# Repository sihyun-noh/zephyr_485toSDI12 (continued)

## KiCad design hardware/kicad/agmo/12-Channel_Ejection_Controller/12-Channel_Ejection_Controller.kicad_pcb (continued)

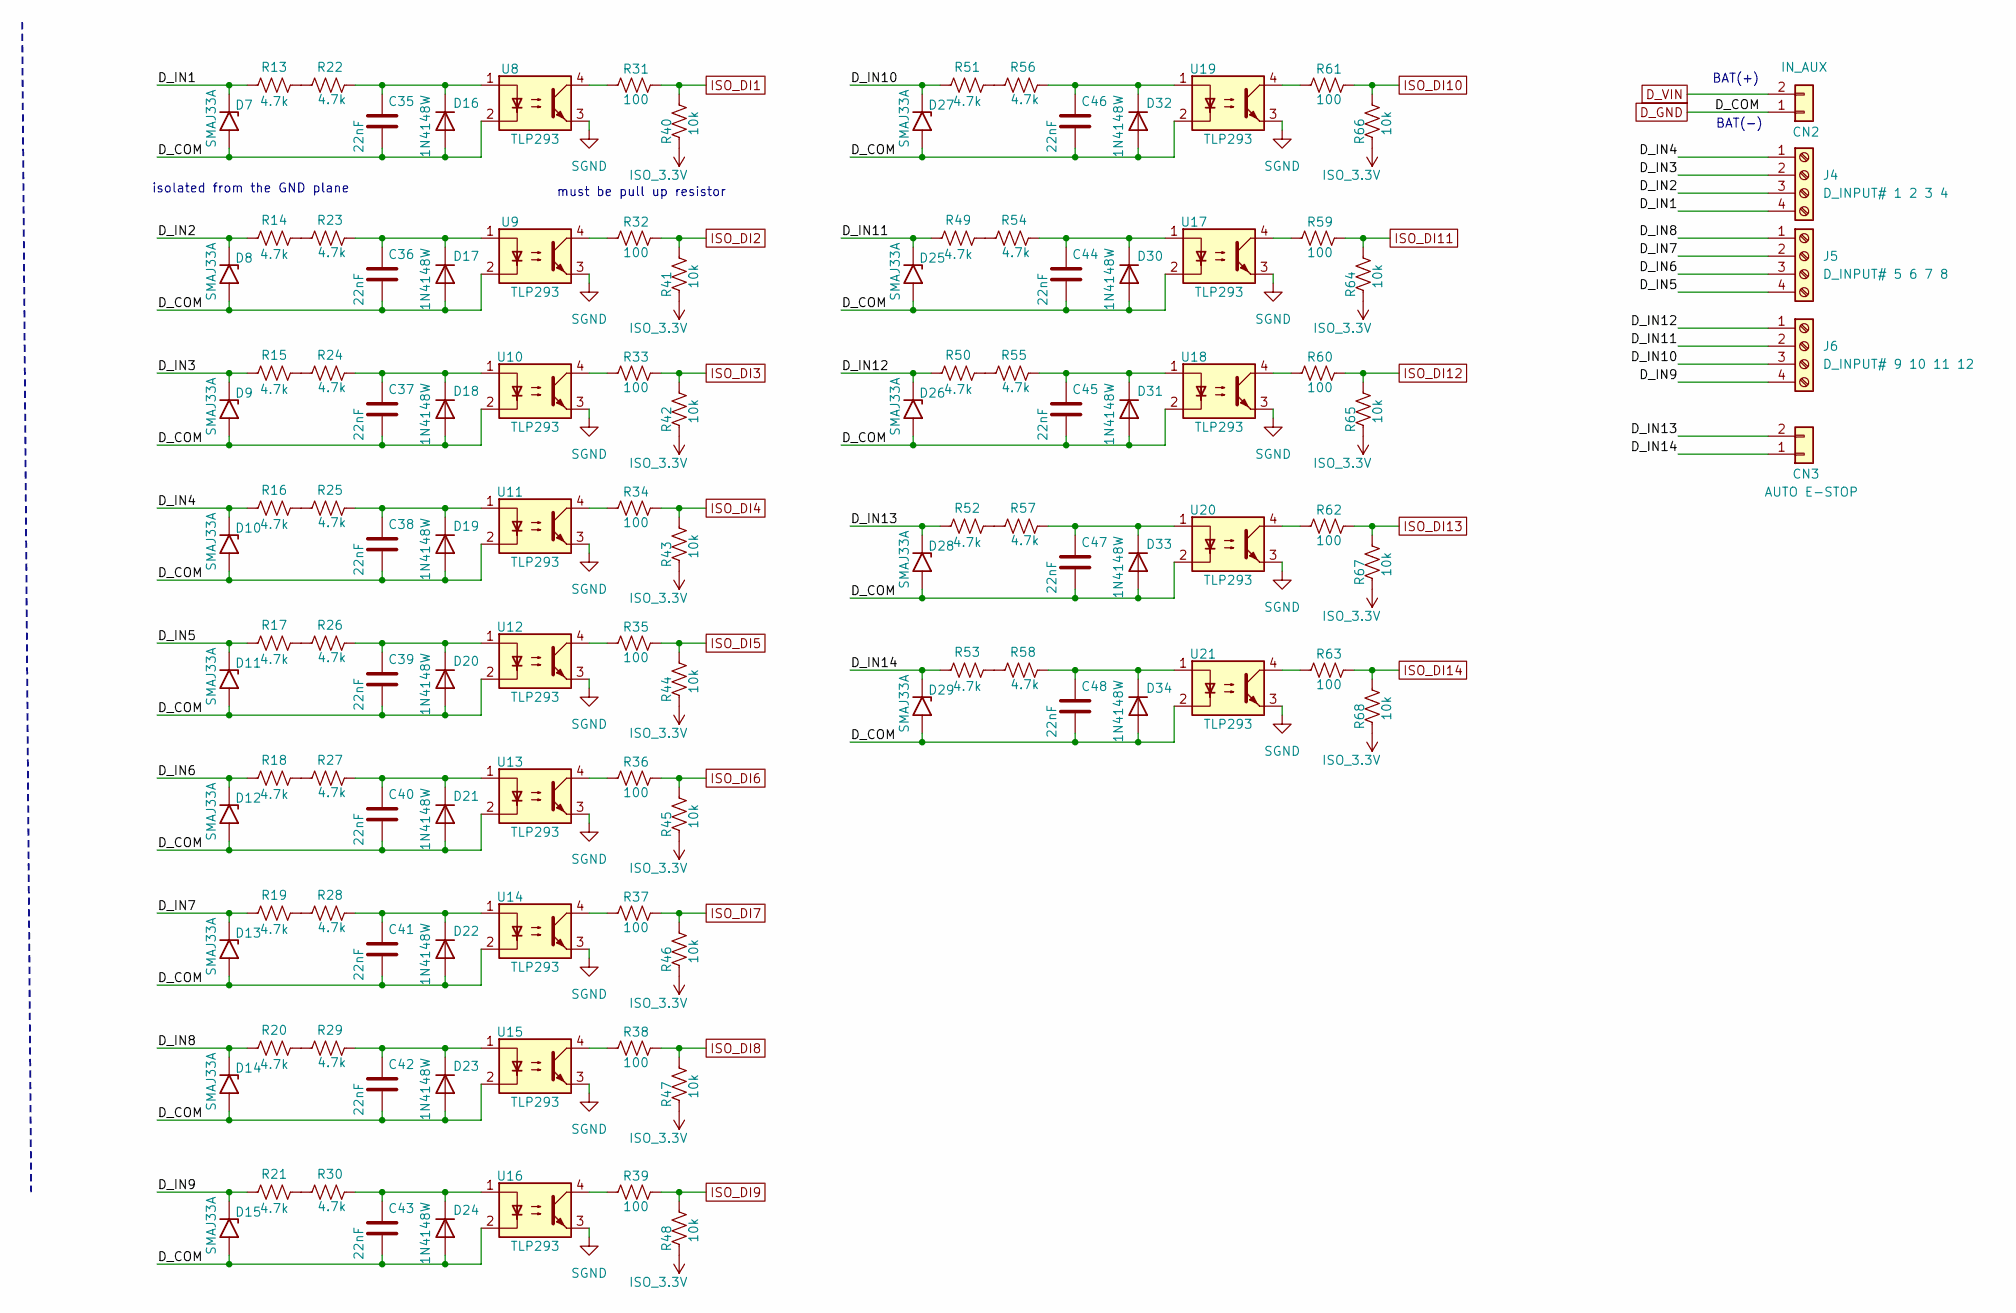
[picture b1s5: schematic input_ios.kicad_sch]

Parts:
C35, C36, C37, C38, C39, C40, C41, C42, C43, C44, C45, C46, C47, C48: 22nF; C_0805_2012Metric_Pad1.18x1.45mm_HandSolder
CN2: IN_AUX; PhoenixContact_MSTBA_2,5_2-G-5,08_1x02_P5.08mm_Horizontal; LCSC C395737
CN3: AUTO E-STOP; PhoenixContact_MSTBA_2,5_2-G-5,08_1x02_P5.08mm_Horizontal; LCSC C395737
D7, D8, D9, D10, D11, D12, D13, D14, D15, D25, D26, D27, D28, D29: SMAJ33A; D_SMA
D16, D17, D18, D19, D20, D21, D22, D23, D24, D30, D31, D32, D33, D34: 1N4148W; D_SOD-123
J4: D_INPUT# 1 2 3 4; PhoenixContact_MSTBA_2,5_4-G-5,08_1x04_P5.08mm_Horizontal; LCSC C395753
J5: D_INPUT# 5 6 7 8; PhoenixContact_MSTBA_2,5_4-G-5,08_1x04_P5.08mm_Horizontal; LCSC C395753
J6: D_INPUT# 9 10 11 12; PhoenixContact_MSTBA_2,5_4-G-5,08_1x04_P5.08mm_Horizontal; LCSC C395753
R13, R14, R15, R16, R17, R18, R19, R20, R21, R22, R23, R24, R25, R26, R27, R28, R29, R30, R49, R50, R51, R52, R53, R54, R55, R56, R57, R58: 4.7k; R_0805_2012Metric
R31, R32, R33, R34, R35, R36, R37, R38, R39, R59, R60, R61, R62, R63: 100; R_0805_2012Metric
R40, R41, R42, R43, R44, R45, R46, R47, R48, R64, R65, R66, R67, R68: 10k; R_0805_2012Metric
U8, U9, U10, U11, U12, U13, U14, U15, U16, U17, U18, U19, U20, U21: TLP293; SOIC-4_4.55x2.6mm_P1.27mm; LCSC C77656

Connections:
/input_ios Sheet/D_IN1: D7.1 (A1), J4.4, R13.1
/input_ios Sheet/D_IN2: D8.1 (A1), J4.3, R14.1
/input_ios Sheet/D_IN3: D9.1 (A1), J4.2, R15.1
/input_ios Sheet/D_IN4: D10.1 (A1), J4.1, R16.1
/input_ios Sheet/D_IN5: D11.1 (A1), J5.4, R17.1
/input_ios Sheet/D_IN6: D12.1 (A1), J5.3, R18.1
/input_ios Sheet/D_IN7: D13.1 (A1), J5.2, R19.1
/input_ios Sheet/D_IN8: D14.1 (A1), J5.1, R20.1
/input_ios Sheet/D_IN9: D15.1 (A1), J6.4, R21.1
/input_ios Sheet/D_IN10: D27.1 (A1), J6.3, R51.1
/input_ios Sheet/D_IN11: D25.1 (A1), J6.2, R49.1
/input_ios Sheet/D_IN12: D26.1 (A1), J6.1, R50.1
/input_ios Sheet/D_IN13: CN3.2, D28.1 (A1), R52.1
/input_ios Sheet/D_IN14: CN3.1, D29.1 (A1), R53.1
D_GND: C35.2, C36.2, C37.2, C38.2, C39.2, C40.2, C41.2, C42.2, C43.2, C44.2, C45.2, C46.2, C47.2, C48.2, CN2.1, D7.2 (A2), D8.2 (A2), D9.2 (A2), D10.2 (A2), D11.2 (A2), D12.2 (A2), D13.2 (A2), D14.2 (A2), D15.2 (A2), D16.2 (A), D17.2 (A), D18.2 (A), D19.2 (A), D20.2 (A), D21.2 (A), D22.2 (A), D23.2 (A), D24.2 (A), D25.2 (A2), D26.2 (A2), D27.2 (A2), D28.2 (A2), D29.2 (A2), D30.2 (A), D31.2 (A), D32.2 (A), D33.2 (A), D34.2 (A), U8.2, U9.2, U10.2, U11.2, U12.2, U13.2, U14.2, U15.2, U16.2, U17.2, U18.2, U19.2, U20.2, U21.2; also elsewhere on the board
D_VIN: CN2.2; also elsewhere on the board
ISO_3.3V: R40.2, R41.2, R42.2, R43.2, R44.2, R45.2, R46.2, R47.2, R48.2, R64.2, R65.2, R66.2, R67.2, R68.2; also elsewhere on the board
ISO_DI1: R31.1, R40.1; also elsewhere on the board
ISO_DI2: R32.1, R41.1; also elsewhere on the board
ISO_DI3: R33.1, R42.1; also elsewhere on the board
ISO_DI4: R34.1, R43.1; also elsewhere on the board
ISO_DI5: R35.1, R44.1; also elsewhere on the board
ISO_DI6: R36.1, R45.1; also elsewhere on the board
ISO_DI7: R37.1, R46.1; also elsewhere on the board
ISO_DI8: R38.1, R47.1; also elsewhere on the board
ISO_DI9: R39.1, R48.1; also elsewhere on the board
ISO_DI10: R61.1, R66.1; also elsewhere on the board
ISO_DI11: R59.1, R64.1; also elsewhere on the board
ISO_DI12: R60.1, R65.1; also elsewhere on the board
ISO_DI13: R62.1, R67.1; also elsewhere on the board
ISO_DI14: R63.1, R68.1; also elsewhere on the board
unnamed: C35.1, D16.1 (K), R22.2, U8.1
unnamed: C36.1, D17.1 (K), R23.2, U9.1
unnamed: C37.1, D18.1 (K), R24.2, U10.1
unnamed: C38.1, D19.1 (K), R25.2, U11.1
unnamed: C39.1, D20.1 (K), R26.2, U12.1
unnamed: C40.1, D21.1 (K), R27.2, U13.1
unnamed: C41.1, D22.1 (K), R28.2, U14.1
unnamed: C42.1, D23.1 (K), R29.2, U15.1
unnamed: C43.1, D24.1 (K), R30.2, U16.1
unnamed: C44.1, D30.1 (K), R54.2, U17.1
unnamed: C45.1, D31.1 (K), R55.2, U18.1
unnamed: C46.1, D32.1 (K), R56.2, U19.1
unnamed: C47.1, D33.1 (K), R57.2, U20.1
unnamed: C48.1, D34.1 (K), R58.2, U21.1
unnamed: R13.2, R22.1
unnamed: R14.2, R23.1
unnamed: R15.2, R24.1
unnamed: R16.2, R25.1
unnamed: R17.2, R26.1
unnamed: R18.2, R27.1
unnamed: R19.2, R28.1
unnamed: R20.2, R29.1
unnamed: R21.2, R30.1
unnamed: R31.2, U8.4
unnamed: R32.2, U9.4
unnamed: R33.2, U10.4
unnamed: R34.2, U11.4
unnamed: R35.2, U12.4
unnamed: R36.2, U13.4
unnamed: R37.2, U14.4
unnamed: R38.2, U15.4
unnamed: R39.2, U16.4
unnamed: R49.2, R54.1
unnamed: R50.2, R55.1
unnamed: R51.2, R56.1
unnamed: R52.2, R57.1
unnamed: R53.2, R58.1
unnamed: R59.2, U17.4
unnamed: R60.2, U18.4
unnamed: R61.2, U19.4
unnamed: R62.2, U20.4
unnamed: R63.2, U21.4
SGND: U8.3, U9.3, U10.3, U11.3, U12.3, U13.3, U14.3, U15.3, U16.3, U17.3, U18.3, U19.3, U20.3, U21.3; also elsewhere on the board

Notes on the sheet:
isolated from the GND plane
BAT(+)
BAT(-)
must be pull up resistor

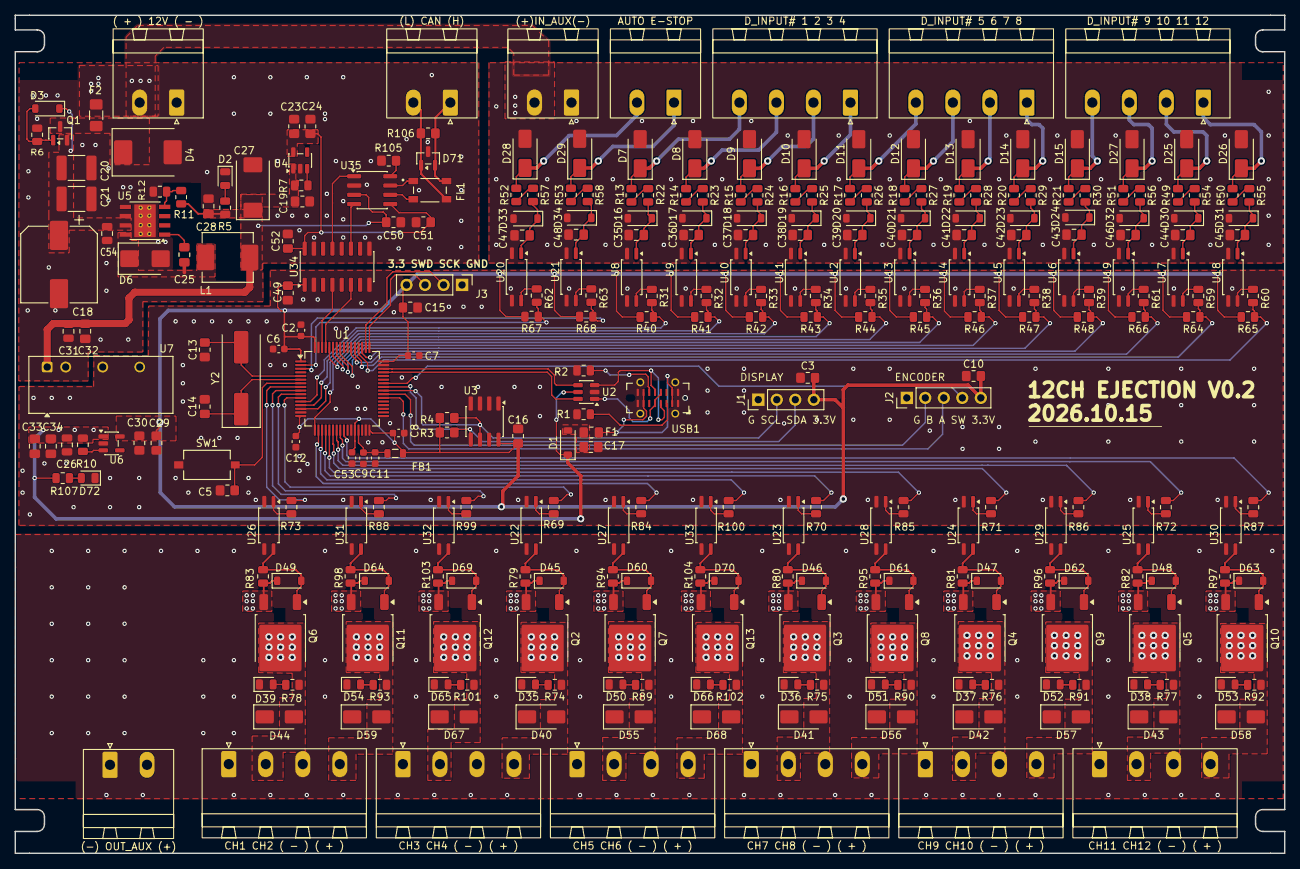
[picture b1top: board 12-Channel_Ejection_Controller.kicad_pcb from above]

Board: 2 copper layers, 174.2 x 115.0 mm, 300 parts (0 on the bottom side), 177 nets.

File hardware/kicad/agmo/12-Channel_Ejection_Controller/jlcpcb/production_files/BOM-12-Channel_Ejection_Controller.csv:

Comment,Designator,Footprint,LCSC,Quantity
( + ) 12V ( - ),CN1,"PhoenixContact_MSTBA_2,5_2-G-5,08_1x02_P5.08mm_Horizontal",C395737,1
(+)IN_AUX(-),CN2,"PhoenixContact_MSTBA_2,5_2-G-5,08_1x02_P5.08mm_Horizontal",C395737,1
(-) OUT_AUX (+),CN5,"PhoenixContact_MSTBA_2,5_2-G-5,08_1x02_P5.08mm_Horizontal",C395737,1
(L) CAN (H),CN4,"PhoenixContact_MSTBA_2,5_2-G-5,08_1x02_P5.08mm_Horizontal",C395737,1
0466005.NRHF,F2,Fuse_1206_3216Metric_Pad1.42x1.75mm_HandSolder,C57525,1
100,"R31,R32,R33,R34,R35,R36,R37,R38,R39,R59,R60,R61,R62,R63",R_0805_2012Metric,C17408,14
100nF,"C12,C2,C53,C6,C7,C8,C9",C_0603_1608Metric,C1591,7
100nF,"C10,C15,C16,C17,C23,C28,C29,C3,C32,C34,C49,C5,C50,C51,C52,C54",R_0805_2012Metric_Pad1.20x1.40mm_HandSolder,C1711,16
10k,"R1,R10,R11,R2,R40,R41,R42,R43,R44,R45,R46,R47,R48,R64,R65,R66,R67,R68,R7",R_0805_2012Metric,C17414,19
10nF,C25,C_0805_2012Metric_Pad1.18x1.45mm_HandSolder,C97905,1
10uF,C33,C_0805_2012Metric_Pad1.18x1.45mm_HandSolder,C15850,1
10uF/50V,C20,C_1812_4532Metric,C76689,1
120,R106,R_0805_2012Metric_Pad1.20x1.40mm_HandSolder,C17437,1
1N4148W,"D16,D17,D18,D19,D20,D21,D22,D23,D24,D30,D31,D32,D33,D34",D_SOD-123,C2099,14
1N5819,D1,D_SOD-123,C963381,1
1k,"R100,R69,R70,R71,R72,R73,R84,R85,R86,R87,R88,R99",R_0805_2012Metric,C17513,12
1uF,C11,C_0603_1608Metric,C15849,1
1uF,"C19,C24,C30",R_0805_2012Metric_Pad1.20x1.40mm_HandSolder,C1712,3
220uF,C27,CP_EIA-7343-31_Kemet-D,C130380,1
220uF/50V,C18,CP_Elec_10x10,C125976,1
22k,"R103,R104,R79,R80,R81,R82,R83,R94,R95,R96,R97,R98",R_0805_2012Metric,C17560,12
22nF,"C35,C36,C37,C38,C39,C40,C41,C42,C43,C44,C45,C46,C47,C48",C_0805_2012Metric_Pad1.18x1.45mm_HandSolder,C1729,14
22pF,"C13,C14",R_0805_2012Metric_Pad1.20x1.40mm_HandSolder,C1804,2
22uH,L1,L_APV_APH0630,C5349702,1
3.24k,R12,R_0805_2012Metric,C17609,1
4.7k,"R101,R102,R107,R13,R14,R15,R16,R17,R18,R19,R20,R21,R22,R23,R24,R25,R26,R27,R28,R29,R3,R30,R4,R49,R5,R50,R51,R52,R53,R54,R55,R56,R57,R58,R6,R74,R75,R76,R77,R78,R89,R90,R91,R92,R93",R_0805_2012Metric,C17673,45
4.7uF,"C26,C31",C_0805_2012Metric,C1779,2
4.7uF/50V,C21,C_1812_4532Metric,C342629,1
600Ω @ 100MHz,FB1,L_0805_2012Metric,C21519,1
8Mhz,Y2,Crystal_SMD_HC49-SD,C12674,1
ACT45B-510-2P-TL003,FL1,FIL_ACT45B-510-2P-TL003,C76584,1
AP2112K-3.3,"U4,U6",SOT-23-5,C51118,2
AT24C256C-SSHL,U3,SOIC-8_3.9x4.9mm_P1.27mm,C615461,1
AUTO E-STOP,CN3,"PhoenixContact_MSTBA_2,5_2-G-5,08_1x02_P5.08mm_Horizontal",C395737,1
B0505S-3W,U7,Converter_DCDC_TRACO_TBA2-xxxx_Single_THT,C7465195,1
B340,D6,D_SMB,C3018525,1
BZT52C15,"D3,D45,D46,D47,D48,D49,D60,D61,D62,D63,D64,D69,D70",D_SOD-123,C2932746,13
CH1 CH2 ( - ) ( + ),J7,"PhoenixContact_MSTBA_2,5_4-G-5,08_1x04_P5.08mm_Horizontal",C395753,1
CH11 CH12 ( - ) ( + ),J12,"PhoenixContact_MSTBA_2,5_4-G-5,08_1x04_P5.08mm_Horizontal",C395753,1
CH3 CH4 ( - ) ( + ),J9,"PhoenixContact_MSTBA_2,5_4-G-5,08_1x04_P5.08mm_Horizontal",C395753,1
CH5 CH6 ( - ) ( + ),J11,"PhoenixContact_MSTBA_2,5_4-G-5,08_1x04_P5.08mm_Horizontal",C395753,1
CH7 CH8 ( - ) ( + ),J8,"PhoenixContact_MSTBA_2,5_4-G-5,08_1x04_P5.08mm_Horizontal",C395753,1
CH9 CH10 ( - ) ( + ),J10,"PhoenixContact_MSTBA_2,5_4-G-5,08_1x04_P5.08mm_Horizontal",C395753,1
DMP10H400SK3-13,"Q10,Q11,Q12,Q13,Q2,Q3,Q4,Q5,Q6,Q7,Q8,Q9",TO-252-2,C177034,12
D_INPUT# 1 2 3 4,J4,"PhoenixContact_MSTBA_2,5_4-G-5,08_1x04_P5.08mm_Horizontal",C395753,1
D_INPUT# 5 6 7 8,J5,"PhoenixContact_MSTBA_2,5_4-G-5,08_1x04_P5.08mm_Horizontal",C395753,1
D_INPUT# 9 10 11 12,J6,"PhoenixContact_MSTBA_2,5_4-G-5,08_1x04_P5.08mm_Horizontal",C395753,1
Debug,J3,PinHeader_1x04_P2.54mm_Vertical,C53207327,1
LED RED,"D2,D35,D36,D37,D38,D39,D50,D51,D52,D53,D54,D65,D66,D72",LED_0805_2012Metric,C2297,14
MF-PSMF050X-2,F1,C_0805_2012Metric_Pad1.18x1.45mm_HandSolder,C116170,1
NRST,SW1,SW_Tactile_SPST_NO_Straight_CK_PTS636Sx25SMTRLFS,C42420257,1
SM24CANB-02HTG,D71,SOT-23,C151237,1
SMAJ30CA,"D40,D41,D42,D43,D44,D55,D56,D57,D58,D59,D67,D68",D_SMA,C83322,12
SMAJ33A,"D10,D11,D12,D13,D14,D15,D25,D26,D27,D28,D29,D7,D8,D9",D_SMA,C223988,14
SMCJ18AC,D4,D_SMC,C374030,1
SQ2361CEES-T1_GE3,Q1,SOT-23,C29267586,1
SSD1309,J1,PinHeader_1x04_P2.54mm_Vertical,C53207327,1
STM32G473RCT6,U1,LQFP-64_10x10mm_P0.5mm,C529361,1
TJA1051T-3,U35,SOIC-8_3.9x4.9mm_P1.27mm,C38695,1
TLP293,"U10,U11,U12,U13,U14,U15,U16,U17,U18,U19,U20,U21,U22,U23,U24,U25,U26,U27,U28,U29,U30,U31,U32,U33,U8,U9",SOIC-4_4.55x2.6mm_P1.27mm,C77656,26
TPS5430DDA,U5,TI_SO-PowerPAD-8_ThermalVias,C9864,1
USBLC6-2SC6,U2,SOT-23-6,C2827654,1
USB_C_Receptacle_USB2.0_16P,USB1,USB_C_Receptacle_G-Switch_GT-USB-7051x,C2843970,1
encoder-key,J2,PinHeader_1x05_P2.54mm_Vertical,C53207329,1
π142M31,U34,SOIC-16_3.9x9.9mm_P1.27mm,C471606,1
0/J,R105,R_0805_2012Metric_Pad1.20x1.40mm_HandSolder,,1

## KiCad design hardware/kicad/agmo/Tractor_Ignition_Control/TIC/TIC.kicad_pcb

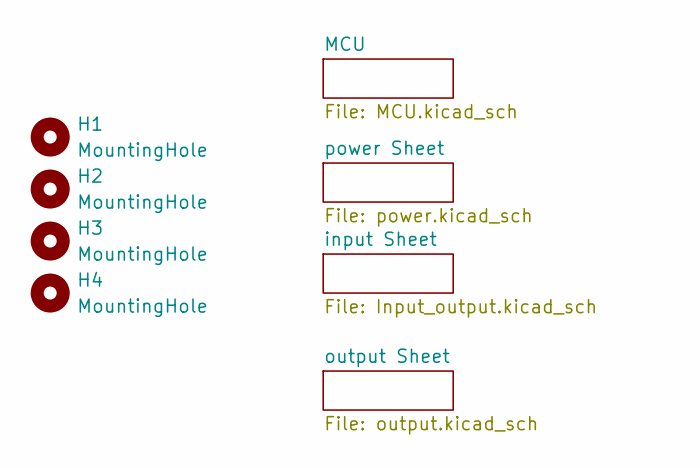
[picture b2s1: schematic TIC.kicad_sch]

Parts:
H1, H2, H3, H4: MountingHole; MountingHole_3.2mm_M3_ISO14580_Pad_TopBottom

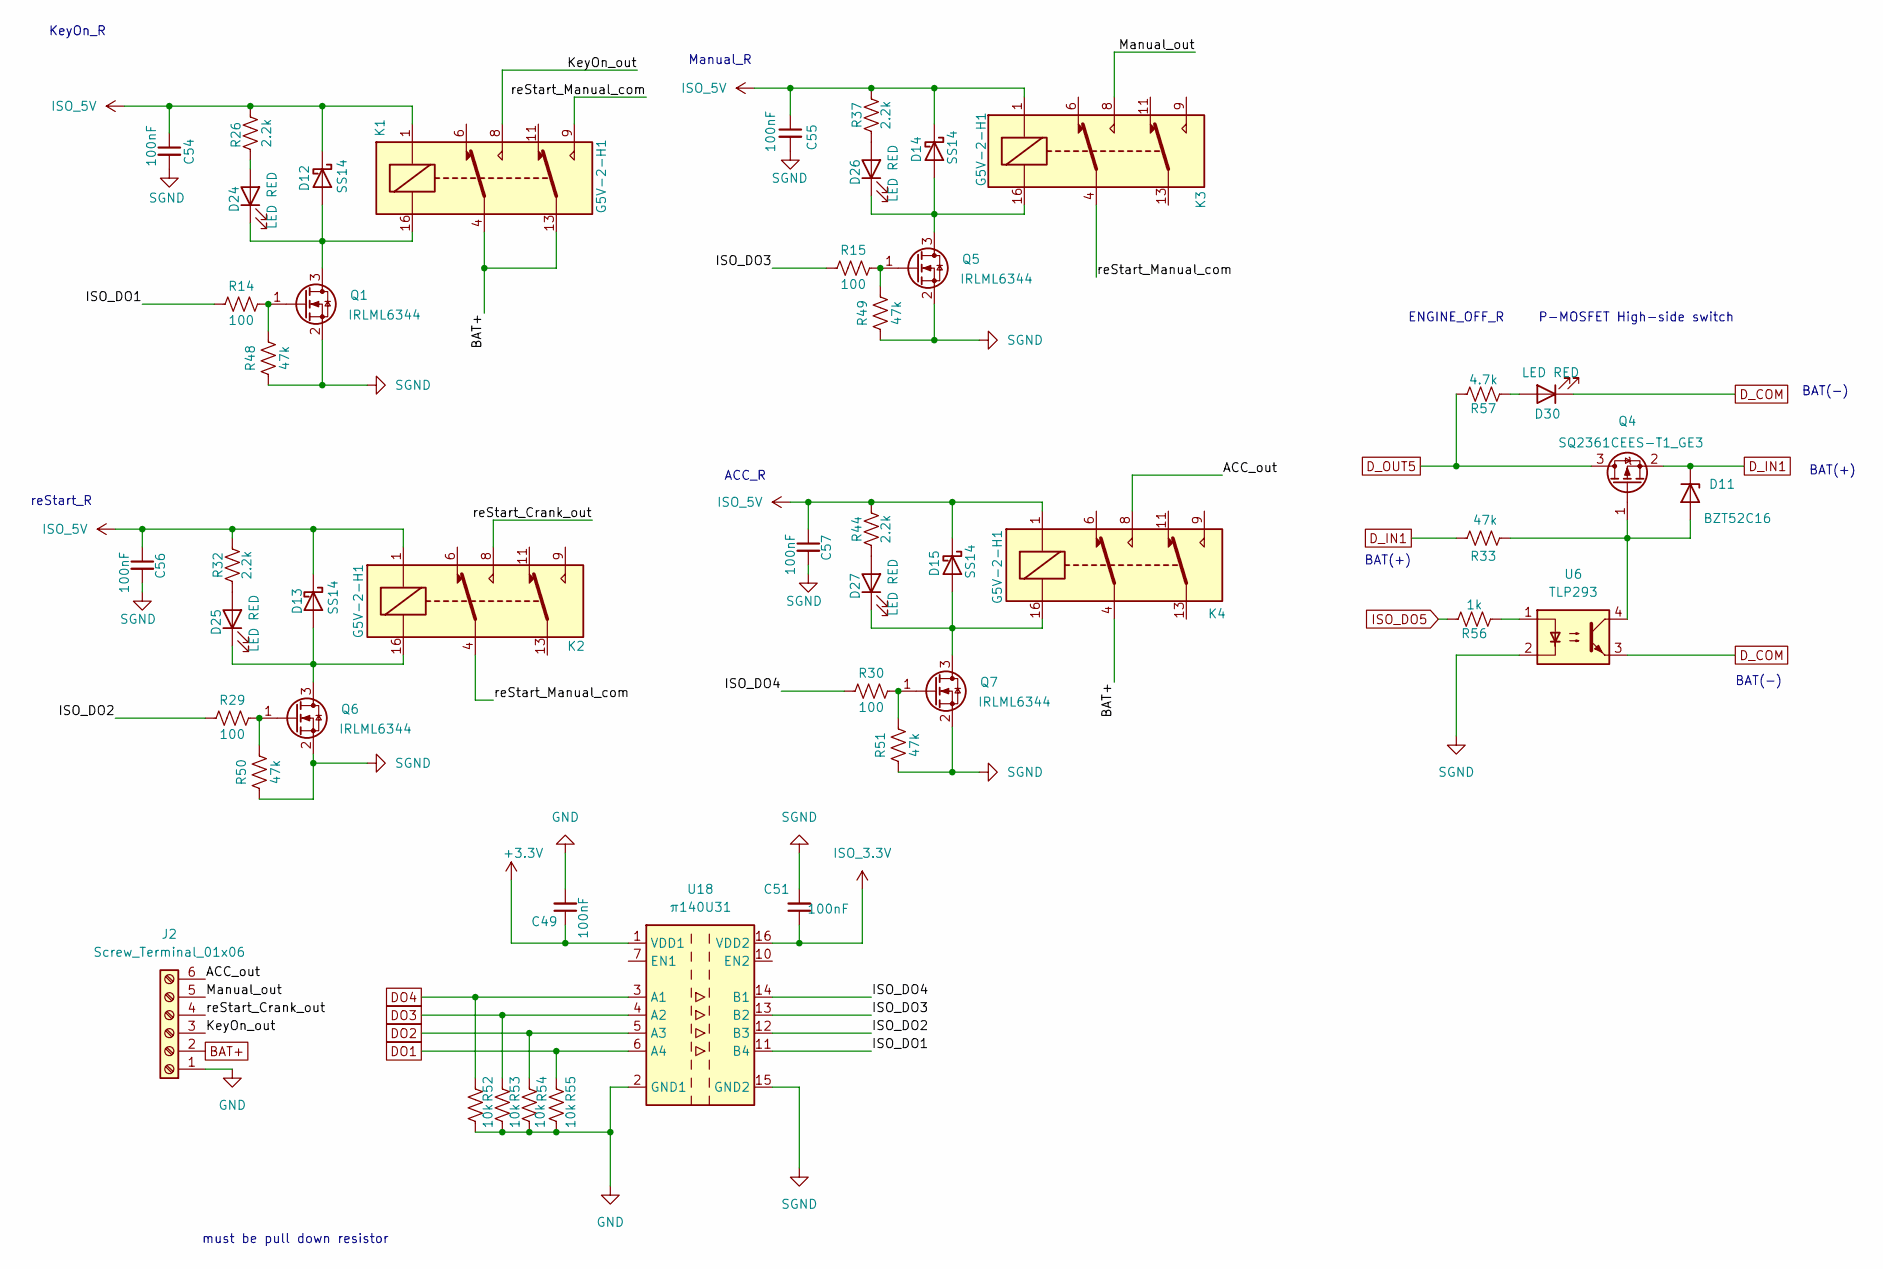
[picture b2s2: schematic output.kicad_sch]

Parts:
C49, C51: 100nF; R_0805_2012Metric_Pad1.20x1.40mm_HandSolder
C54, C55, C56, C57: 100nF; C_0805_2012Metric
D11: BZT52C16; D_SOD-123
D12, D13, D14, D15: SS14; D_SMA
D24, D25, D26, D27, D30: LED RED; LED_0805_2012Metric
J2: Screw_Terminal_01x06; PhoenixContact_MSTBA_2,5_6-G-5,08_1x06_P5.08mm_Horizontal; LCSC C395769
K1, K2, K3, K4: G5V-2-H1; Relay_DPDT_Omron_G5V-2
Q1, Q5, Q6, Q7: IRLML6344; SOT-23; LCSC C53550
Q4: SQ2361CEES-T1_GE3; SOT-23; LCSC C29267586
R14, R15, R29, R30: 100; R_0805_2012Metric
R26, R32, R37, R44: 2.2k; R_0805_2012Metric
R33, R48, R49, R50, R51: 47k; R_0805_2012Metric
R52, R53, R54, R55: 10k; R_0805_2012Metric
R56: 1k; R_0805_2012Metric
R57: 4.7k; R_0805_2012Metric
U6: TLP293; SOIC-4_4.55x2.6mm_P1.27mm; LCSC C77656
U18: π140U31; SOIC-16_3.9x9.9mm_P1.27mm; LCSC C471601

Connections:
+3.3V: C49.1, U18.1 (VDD1); also elsewhere on the board
/output Sheet/ACC_out: J2.6, K4.8
/output Sheet/ISO_DO1: R14.1, U18.11 (B4)
/output Sheet/ISO_DO2: R29.1, U18.12 (B3)
/output Sheet/ISO_DO3: R15.1, U18.13 (B2)
/output Sheet/ISO_DO4: R30.1, U18.14 (B1)
/output Sheet/KeyOn_out: J2.3, K1.8
/output Sheet/Manual_out: J2.5, K3.8
/output Sheet/reStart_Crank_out: J2.4, K2.8
/output Sheet/reStart_Manual_com: K1.9, K2.4, K3.4
DO1: R55.2, U18.6 (A4); also elsewhere on the board
DO2: R54.2, U18.5 (A3); also elsewhere on the board
DO3: R53.2, U18.4 (A2); also elsewhere on the board
DO4: R52.2, U18.3 (A1); also elsewhere on the board
D_COM: D30.1 (K), U6.3; also elsewhere on the board
D_IN1: D11.1 (K), Q4.2 (S), R33.2; also elsewhere on the board
D_OUT5: Q4.3 (D), R57.1; also elsewhere on the board
ISO_3.3V: C51.1, U18.16 (VDD2); also elsewhere on the board
ISO_5V: C54.1, C55.1, C56.1, C57.1, D12.1 (K), D13.1 (K), D14.1 (K), D15.1 (K), K1.1, K2.1, K3.1, K4.1, R26.1, R32.1, R37.1, R44.1; also elsewhere on the board
ISO_DO5: R56.1; also elsewhere on the board
unnamed: D11.2 (A), Q4.1 (G), R33.1, U6.4
unnamed: D12.2 (A), D24.1 (K), K1.16, Q1.3 (D)
unnamed: D13.2 (A), D25.1 (K), K2.16, Q6.3 (D)
unnamed: D14.2 (A), D26.1 (K), K3.16, Q5.3 (D)
unnamed: D15.2 (A), D27.1 (K), K4.16, Q7.3 (D)
unnamed: D24.2 (A), R26.2
unnamed: D25.2 (A), R32.2
unnamed: D26.2 (A), R37.2
unnamed: D27.2 (A), R44.2
unnamed: D30.2 (A), R57.2
unnamed: Q1.1 (G), R14.2, R48.2
unnamed: Q5.1 (G), R15.2, R49.2
unnamed: Q6.1 (G), R29.2, R50.2
unnamed: Q7.1 (G), R30.2, R51.2
unnamed: R56.2, U6.1
SGND: C51.2, C54.2, C55.2, C56.2, C57.2, Q1.2 (S), Q5.2 (S), Q6.2 (S), Q7.2 (S), R48.1, R49.1, R50.1, R51.1, U6.2, U18.9 (GND2), U18.15 (GND2); also elsewhere on the board

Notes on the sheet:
ACC_R
Manual_R
must be pull down resistor
BAT(-)
KeyOn_R
reStart_R
ENGINE_OFF_R
P-MOSFET High-side switch
BAT(+)

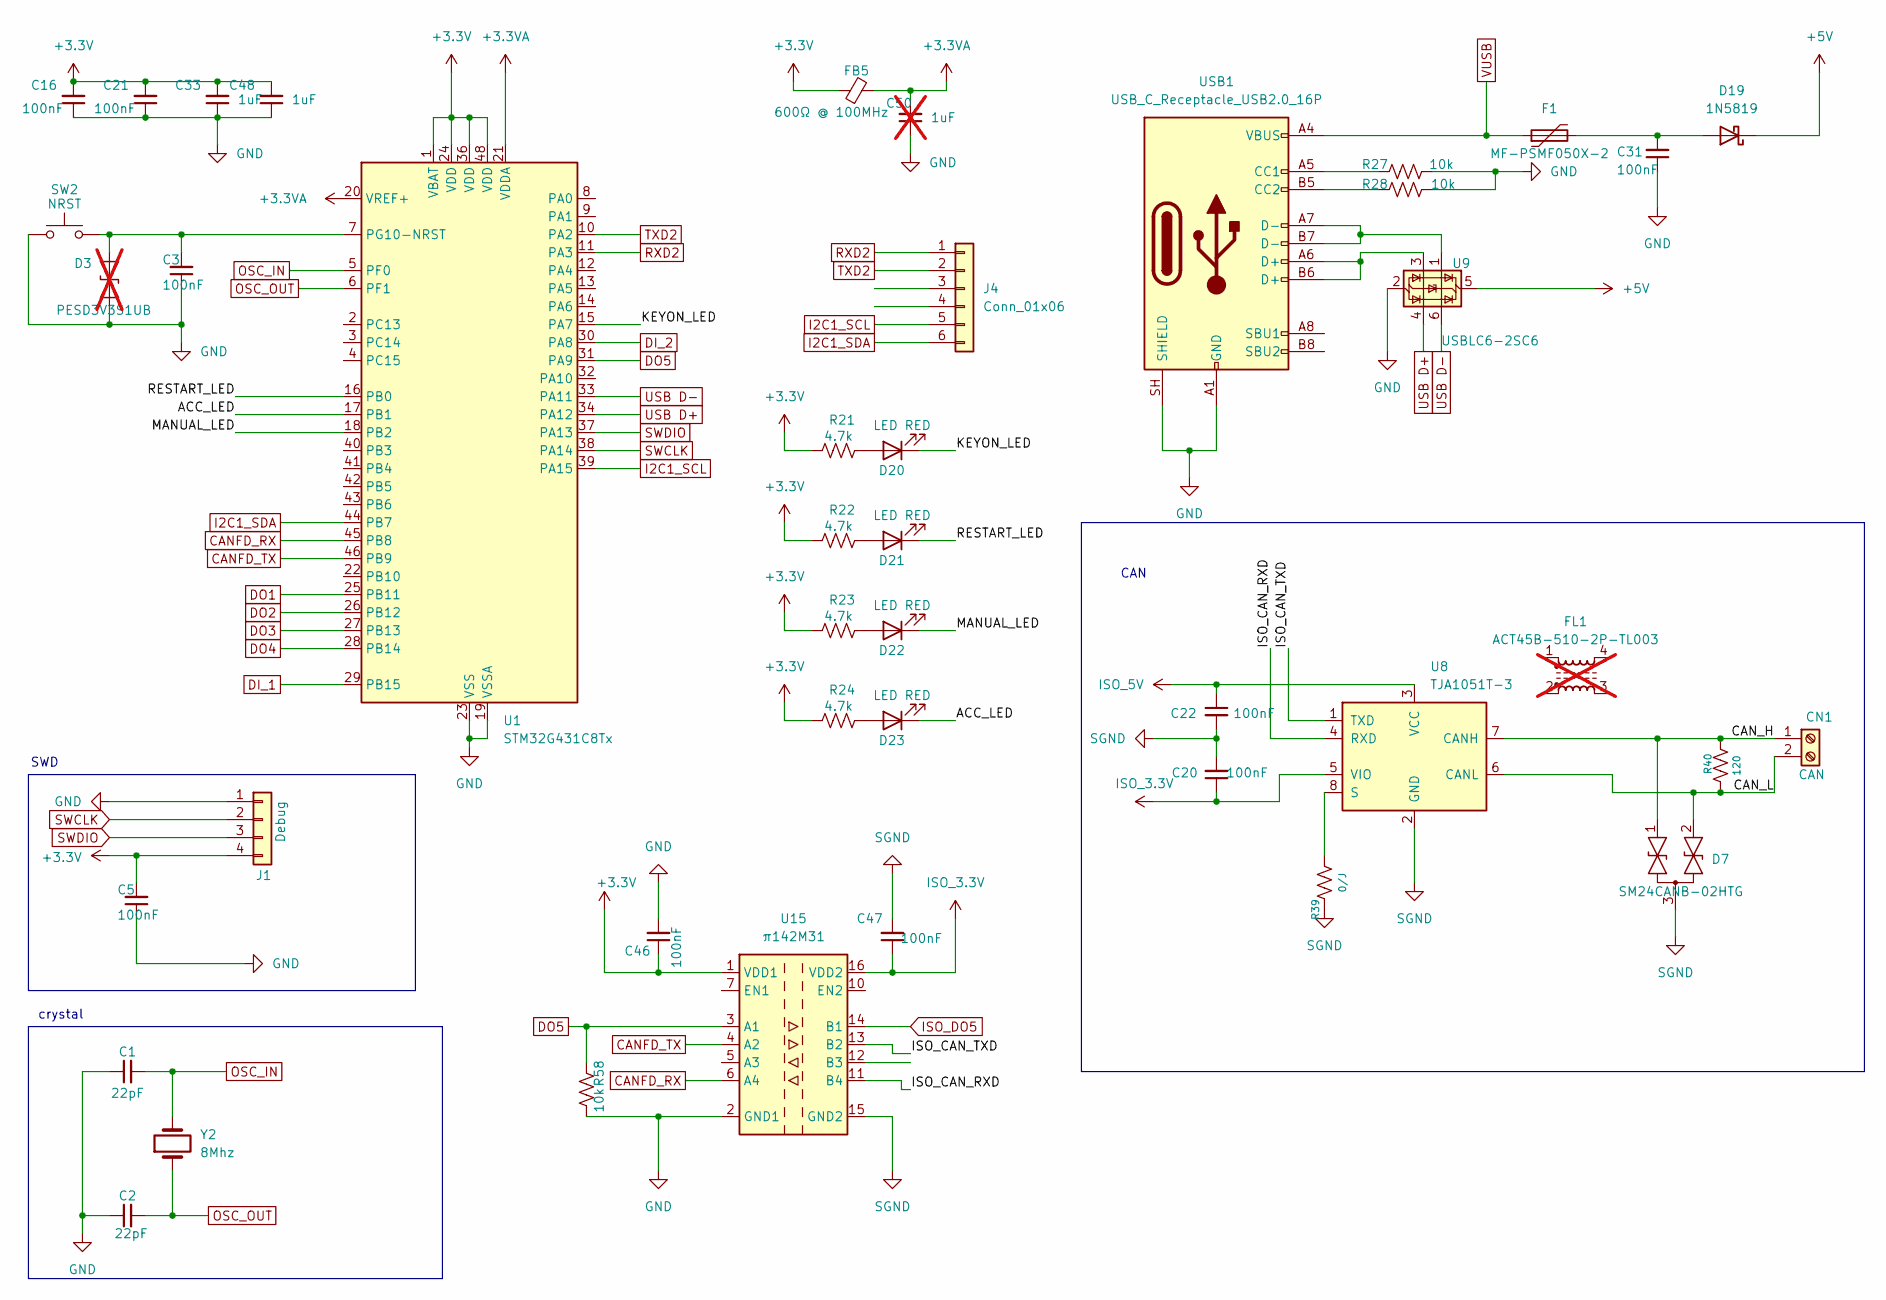
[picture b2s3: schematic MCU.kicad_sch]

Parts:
C1, C2: 22pF; R_0805_2012Metric_Pad1.20x1.40mm_HandSolder
C3, C5, C16, C20, C21, C22, C31, C46, C47: 100nF; R_0805_2012Metric_Pad1.20x1.40mm_HandSolder
C33, C48: 1uF; R_0805_2012Metric_Pad1.20x1.40mm_HandSolder
C50: 1uF; R_0805_2012Metric_Pad1.20x1.40mm_HandSolder; not fitted
CN1: CAN; PhoenixContact_MSTBA_2,5_2-G-5,08_1x02_P5.08mm_Horizontal; LCSC C395737
D3: PESD3V3S1UB; D_SOD-923; LCSC C7436896; not fitted
D7: SM24CANB-02HTG; SOT-23
D19: 1N5819; D_SOD-323
D20, D21, D22, D23: LED RED; LED_0805_2012Metric
F1: MF-PSMF050X-2; C_0805_2012Metric_Pad1.18x1.45mm_HandSolder; LCSC C116170
FB5: 600Ω @ 100MHz; L_0805_2012Metric_Pad1.05x1.20mm_HandSolder; LCSC C81034
FL1: ACT45B-510-2P-TL003; L_CommonModeChoke_Coilank_ACM3216; not fitted
J1: Debug; PinHeader_1x04_P2.54mm_Vertical
J4: Conn_01x06
R21, R22, R23, R24: 4.7k; R_0805_2012Metric
R27, R28, R58: 10k; R_0805_2012Metric
R39: 0/J; R_0805_2012Metric_Pad1.20x1.40mm_HandSolder
R40: 120; R_0805_2012Metric_Pad1.20x1.40mm_HandSolder
SW2: NRST; SW_Tactile_SPST_NO_Straight_CK_PTS636Sx25SMTRLFS; LCSC C42420257
U1: STM32G431C8Tx; LQFP-48_7x7mm_P0.5mm
U8: TJA1051T-3; SOIC-8_3.9x4.9mm_P1.27mm; LCSC C38695
U9: USBLC6-2SC6; SOT-23-6; LCSC C2827654
U15: π142M31; SOIC-16_3.9x9.9mm_P1.27mm; LCSC C471606
USB1: USB_C_Receptacle_USB2.0_16P; USB_C_Receptacle_G-Switch_GT-USB-7010ASV; LCSC C2988369
Y2: 8Mhz; Crystal_SMD_HC49-SD; LCSC C12674

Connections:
+3.3V: C5.2, C16.2, C21.2, C33.2, C46.1, C48.2, FB5.1, J1.4, R21.2, R22.2, R23.2, R24.2, U1.1 (VBAT), U1.24 (VDD), U1.36 (VDD), U1.48 (VDD), U15.1 (VDD1); also elsewhere on the board
+3.3VA: C50.2, FB5.2, U1.20 (VREF+), U1.21 (VDDA)
+5V: D19.1 (K), U9.5 (VBUS); also elsewhere on the board
/MCU/ACC_LED: D23.1 (K), U1.17 (PB1); also elsewhere on the board
/MCU/CAN_H: CN1.1, D7.1 (A1), R40.2, U8.7 (CANH)
/MCU/CAN_L: CN1.2, D7.2 (A2), R40.1, U8.6 (CANL)
/MCU/ISO_CAN_RXD: U8.4 (RXD), U15.11 (B4)
/MCU/ISO_CAN_TXD: U8.1 (TXD), U15.13 (B2)
/MCU/KEYON_LED: D20.1 (K), U1.15 (PA7); also elsewhere on the board
/MCU/MANUAL_LED: D22.1 (K), U1.18 (PB2); also elsewhere on the board
/MCU/RESTART_LED: D21.1 (K), U1.16 (PB0); also elsewhere on the board
CANFD_RX: U1.45 (PB8), U15.6 (A4)
CANFD_TX: U1.46 (PB9), U15.4 (A2)
DI_1: U1.29 (PB15); also elsewhere on the board
DI_2: U1.30 (PA8); also elsewhere on the board
DO1: U1.25 (PB11); also elsewhere on the board
DO2: U1.26 (PB12); also elsewhere on the board
DO3: U1.27 (PB13); also elsewhere on the board
DO4: U1.28 (PB14); also elsewhere on the board
DO5: R58.2, U1.31 (PA9), U15.3 (A1)
I2C1_SCL: J4.5, U1.39 (PA15)
I2C1_SDA: J4.6, U1.44 (PB7)
ISO_3.3V: C20.1, C47.1, U8.5 (VIO), U15.16 (VDD2); also elsewhere on the board
ISO_5V: C22.1, U8.3 (VCC); also elsewhere on the board
ISO_DO5: U15.14 (B1); also elsewhere on the board
unnamed: C31.2, D19.2 (A), F1.2
unnamed 55: D20.2 (A), R21.1; also elsewhere on the board
unnamed 56: D21.2 (A), R22.1; also elsewhere on the board
unnamed 57: D22.2 (A), R23.1; also elsewhere on the board
unnamed 58: D23.2 (A), R24.1; also elsewhere on the board
unnamed: C3.2, D3.1 (A1), SW2.2, U1.7 (PG10-NRST)
unnamed: R39.2, U8.8 (S)
unnamed: U9.1 (I/O1), USB1.A7 (D-), USB1.B7 (D-)
unnamed: U9.3 (I/O2), USB1.A6 (D+), USB1.B6 (D+)
unnamed: R27.1, USB1.A5 (CC1)
unnamed: R28.1, USB1.B5 (CC2)
OSC_IN: C1.2, U1.5 (PF0), Y2.2
OSC_OUT: C2.2, U1.6 (PF1), Y2.1
RXD2: J4.1, U1.11 (PA3)
SGND: C20.2, C22.2, C47.2, D7.3 (common), R39.1, U8.2 (GND), U15.9 (GND2), U15.15 (GND2); also elsewhere on the board
SWCLK: J1.2, U1.38 (PA14)
SWDIO: J1.3, U1.37 (PA13)
TXD2: J4.2, U1.10 (PA2)
USB D+: U1.34 (PA12), U9.4 (I/O2)
USB D-: U1.33 (PA11), U9.6 (I/O1)
VUSB: F1.1, USB1.A4 (VBUS), USB1.A9 (VBUS), USB1.B4 (VBUS), USB1.B9 (VBUS)

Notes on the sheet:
CAN
crystal
SWD

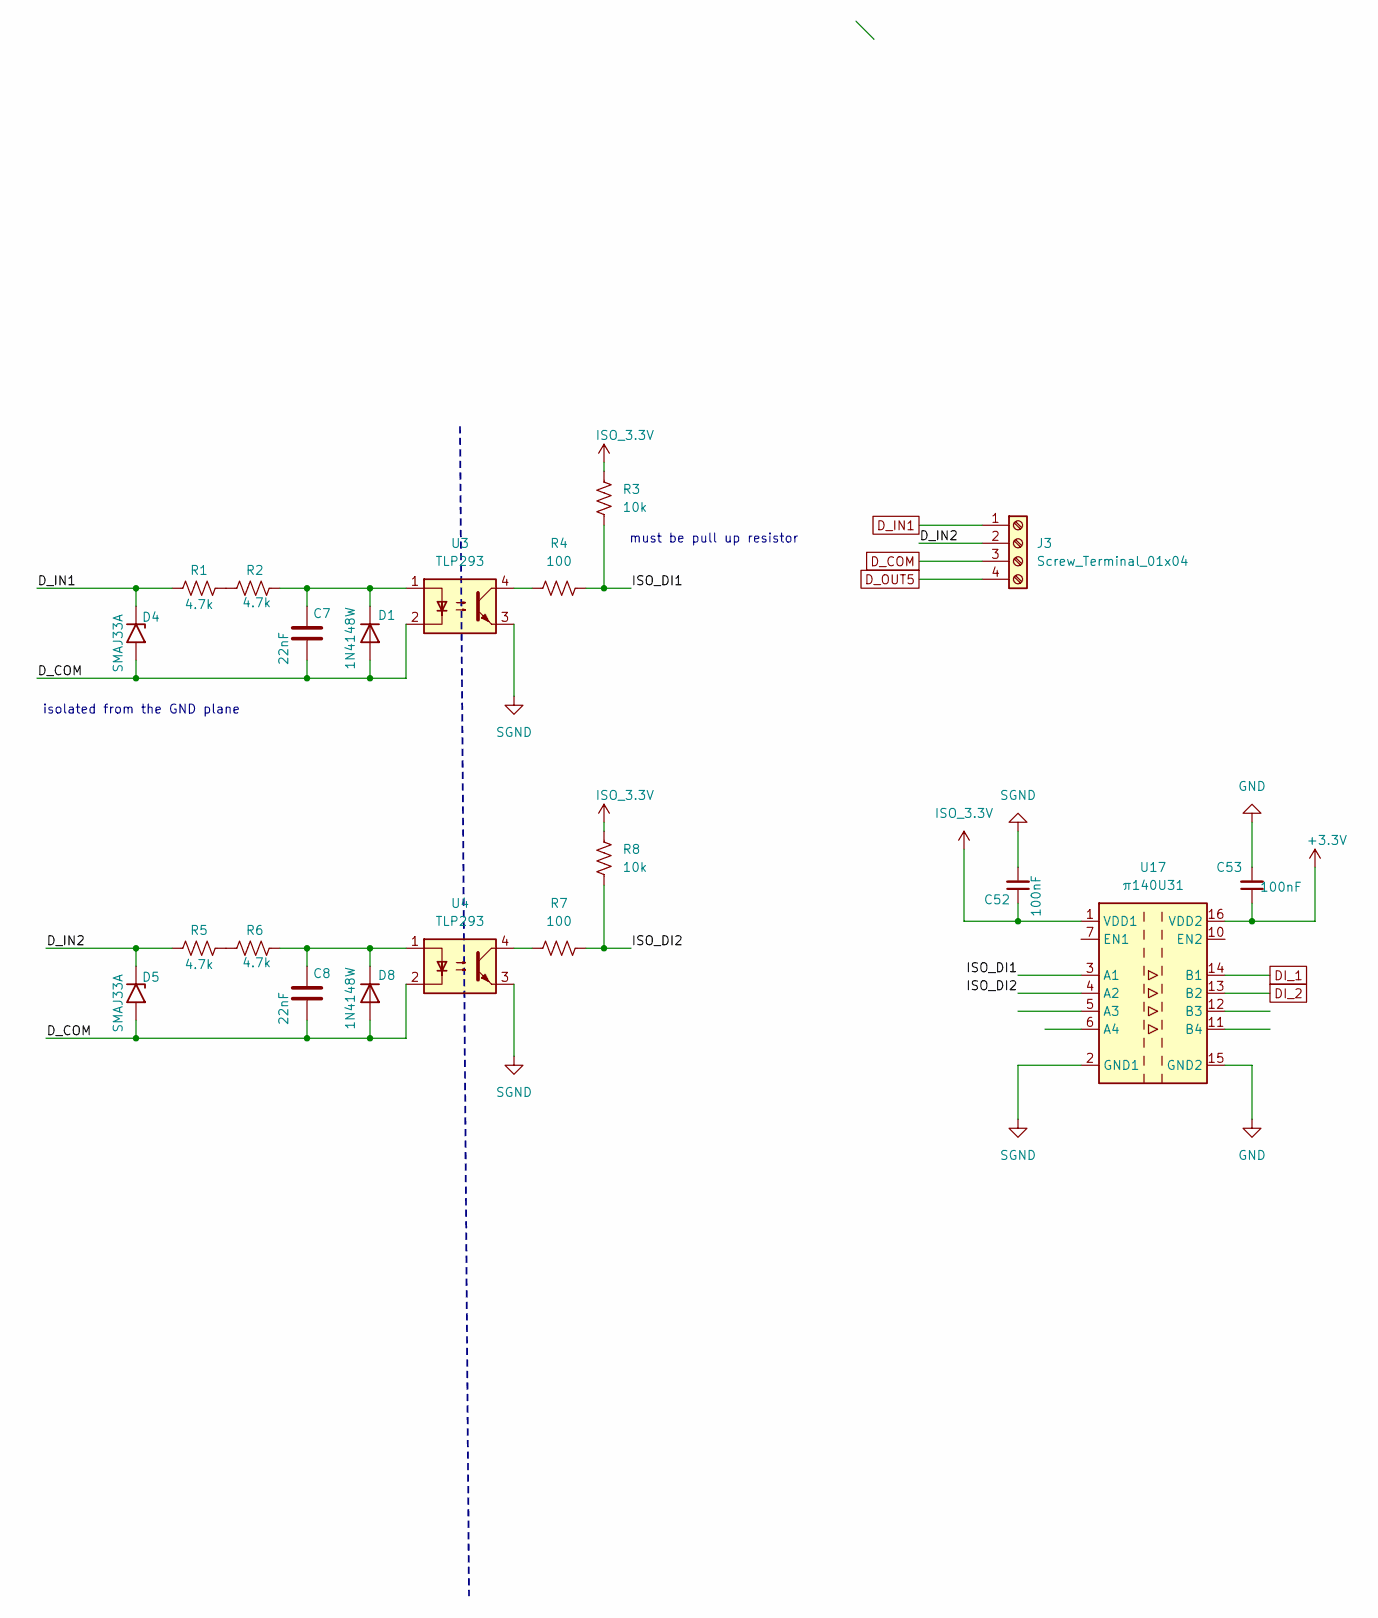
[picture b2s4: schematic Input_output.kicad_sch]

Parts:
C7, C8: 22nF; C_0805_2012Metric_Pad1.18x1.45mm_HandSolder
C52, C53: 100nF; R_0805_2012Metric_Pad1.20x1.40mm_HandSolder
D1, D8: 1N4148W; D_SOD-123
D4, D5: SMAJ33A; D_SMA
J3: Screw_Terminal_01x04; PhoenixContact_MSTBA_2,5_4-G-5,08_1x04_P5.08mm_Horizontal; LCSC C395753
R1, R2, R5, R6: 4.7k; R_0805_2012Metric
R3, R8: 10k; R_0805_2012Metric
R4, R7: 100; R_0805_2012Metric
U3, U4: TLP293; SOIC-4_4.55x2.6mm_P1.27mm; LCSC C77656
U17: π140U31; SOIC-16_3.9x9.9mm_P1.27mm; LCSC C471601

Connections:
+3.3V: C53.1, U17.16 (VDD2); also elsewhere on the board
/input Sheet/D_IN2: D5.1 (A1), J3.2, R5.1
/input Sheet/ISO_DI1: R3.1, R4.1, U17.3 (A1)
/input Sheet/ISO_DI2: R7.1, R8.1, U17.4 (A2)
DI_1: U17.14 (B1); also elsewhere on the board
DI_2: U17.13 (B2); also elsewhere on the board
D_COM: C7.2, C8.2, D1.2 (A), D4.2 (A2), D5.2 (A2), D8.2 (A), J3.3, U3.2, U4.2; also elsewhere on the board
D_IN1: D4.1 (A1), J3.1, R1.1; also elsewhere on the board
D_OUT5: J3.4; also elsewhere on the board
ISO_3.3V: C52.1, R3.2, R8.2, U17.1 (VDD1); also elsewhere on the board
unnamed: C7.1, D1.1 (K), R2.2, U3.1
unnamed: C8.1, D8.1 (K), R6.2, U4.1
unnamed: R1.2, R2.1
unnamed: R4.2, U3.4
unnamed: R5.2, R6.1
unnamed: R7.2, U4.4
SGND: C52.2, U3.3, U4.3, U17.2 (GND1), U17.8 (GND1); also elsewhere on the board

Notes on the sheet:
isolated from the GND plane
must be pull up resistor
